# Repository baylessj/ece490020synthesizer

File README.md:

# ece490020synthesizer
PCB Layout and Schematics for an Analog Synthesizer for ECE Senior Design

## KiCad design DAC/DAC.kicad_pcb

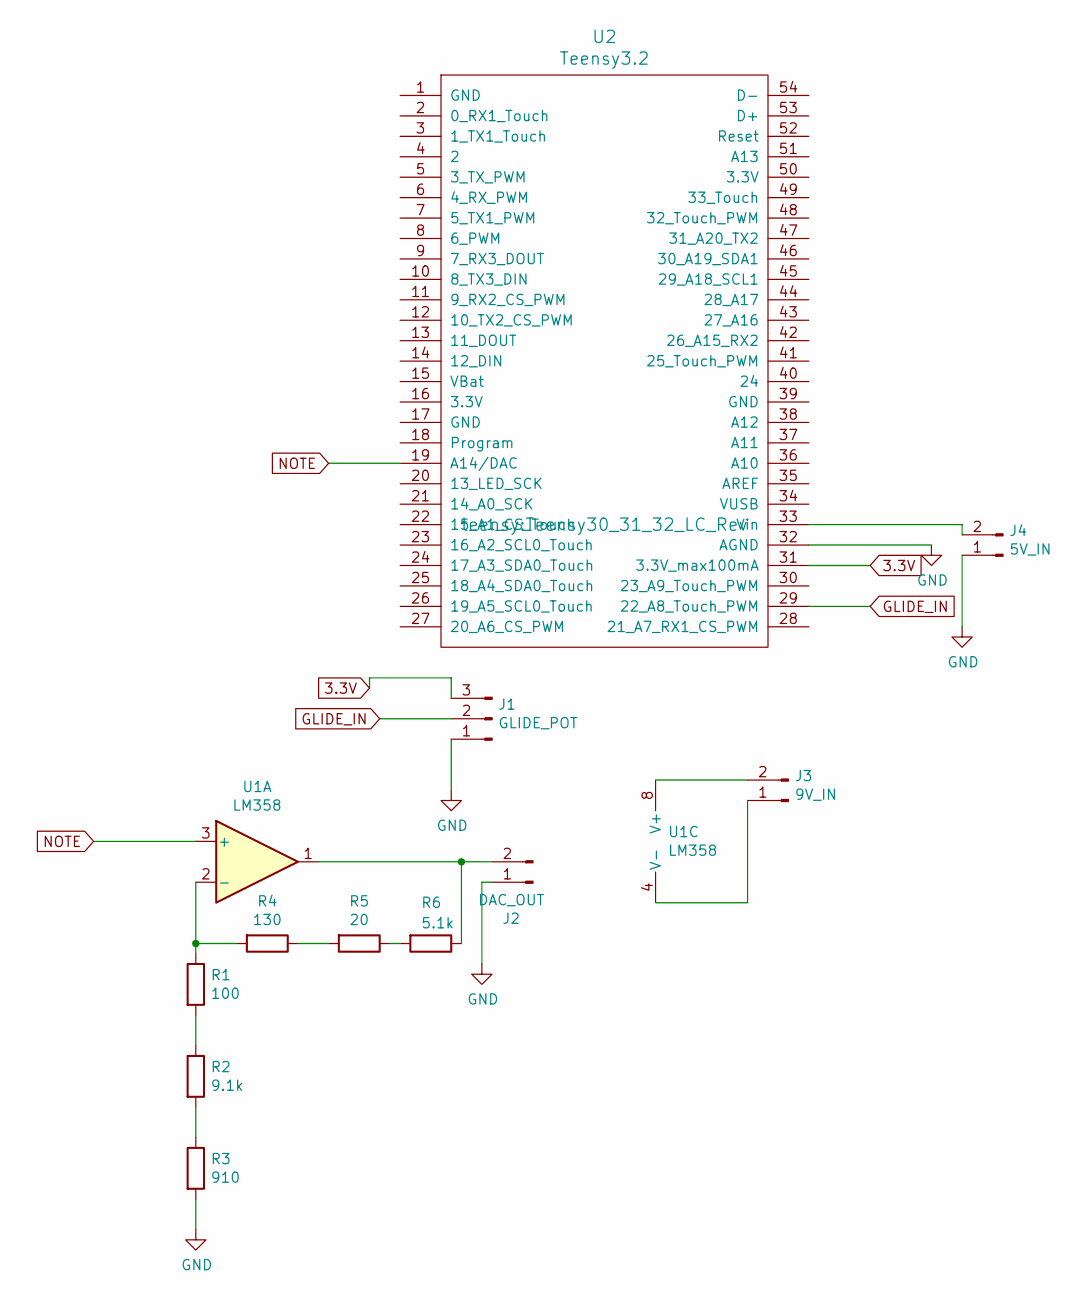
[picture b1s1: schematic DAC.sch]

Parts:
J1: GLIDE_POT; SolderWirePad_1x03_P3.175mm_Drill1mm
J2: DAC_OUT; SolderWirePad_1x02_P3.81mm_Drill1mm
J3: 9V_IN; SolderWirePad_1x02_P3.81mm_Drill1mm
J4: 5V_IN; SolderWirePad_1x02_P3.81mm_Drill1mm
R1: 100; R_Axial_DIN0207_L6.3mm_D2.5mm_P10.16mm_Horizontal
R2: 9.1k; R_Axial_DIN0207_L6.3mm_D2.5mm_P10.16mm_Horizontal
R3: 910; R_Axial_DIN0207_L6.3mm_D2.5mm_P10.16mm_Horizontal
R4: 130; R_Axial_DIN0207_L6.3mm_D2.5mm_P10.16mm_Horizontal
R5: 20; R_Axial_DIN0207_L6.3mm_D2.5mm_P10.16mm_Horizontal
R6: 5.1k; R_Axial_DIN0207_L6.3mm_D2.5mm_P10.16mm_Horizontal
U1: LM358; DIP-8_W7.62mm
U2: Teensy3.2; Teensy30_31_32_LC_Rev

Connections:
3.3V: J1.3, U2.31 (3.3V_max100mA)
GLIDE_IN: J1.2, U2.29 (22_A8_Touch_PWM)
GND: J1.1, J2.1, J4.1, R3.2, U2.32 (AGND)
NOTE: U1.3 (+), U2.19 (A14/DAC)
unnamed: J2.2, R6.1, U1.1
unnamed: J3.1, U1.4 (V-)
unnamed: J3.2, U1.8 (V+)
unnamed: J4.2, U2.33 (Vin)
unnamed: R1.1, R4.2, U1.2 (-)
unnamed: R1.2, R2.1
unnamed: R2.2, R3.1
unnamed: R4.1, R5.2
unnamed: R5.1, R6.2

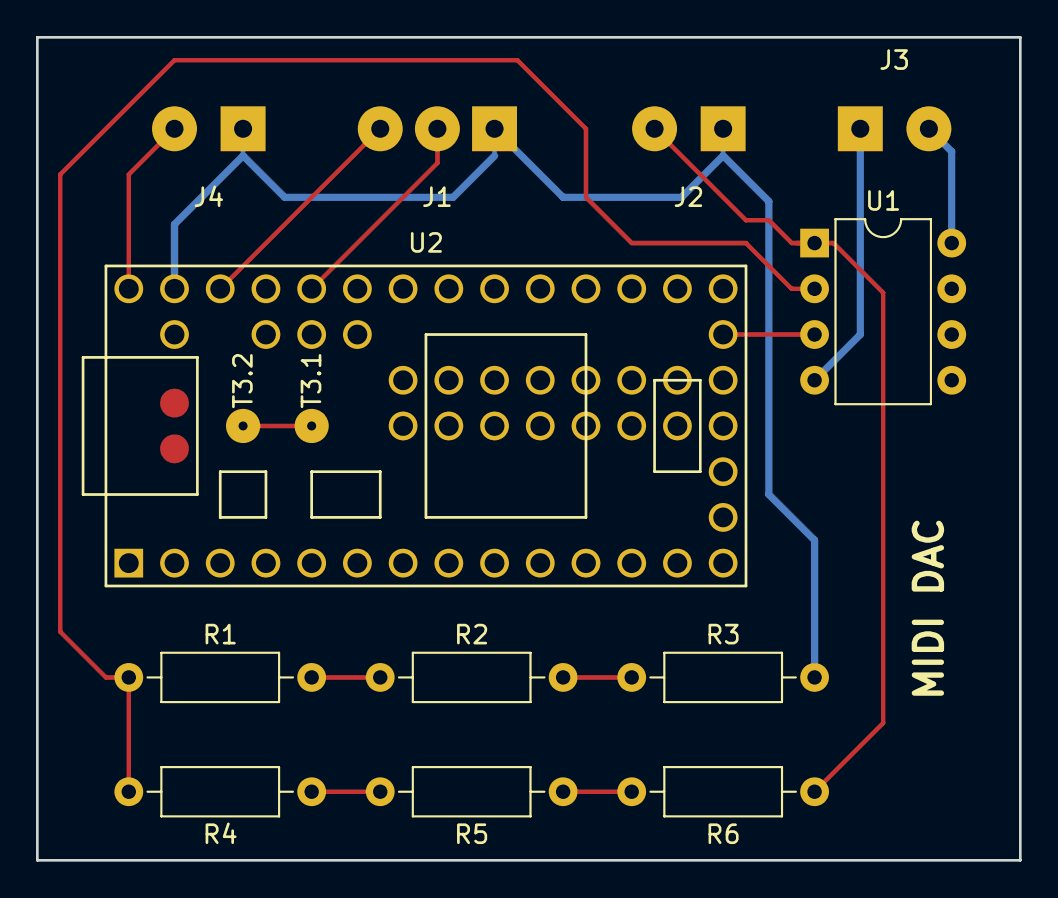
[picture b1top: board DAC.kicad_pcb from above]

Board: 2 copper layers, 54.6 x 45.7 mm, 12 parts (0 on the bottom side), 13 nets.

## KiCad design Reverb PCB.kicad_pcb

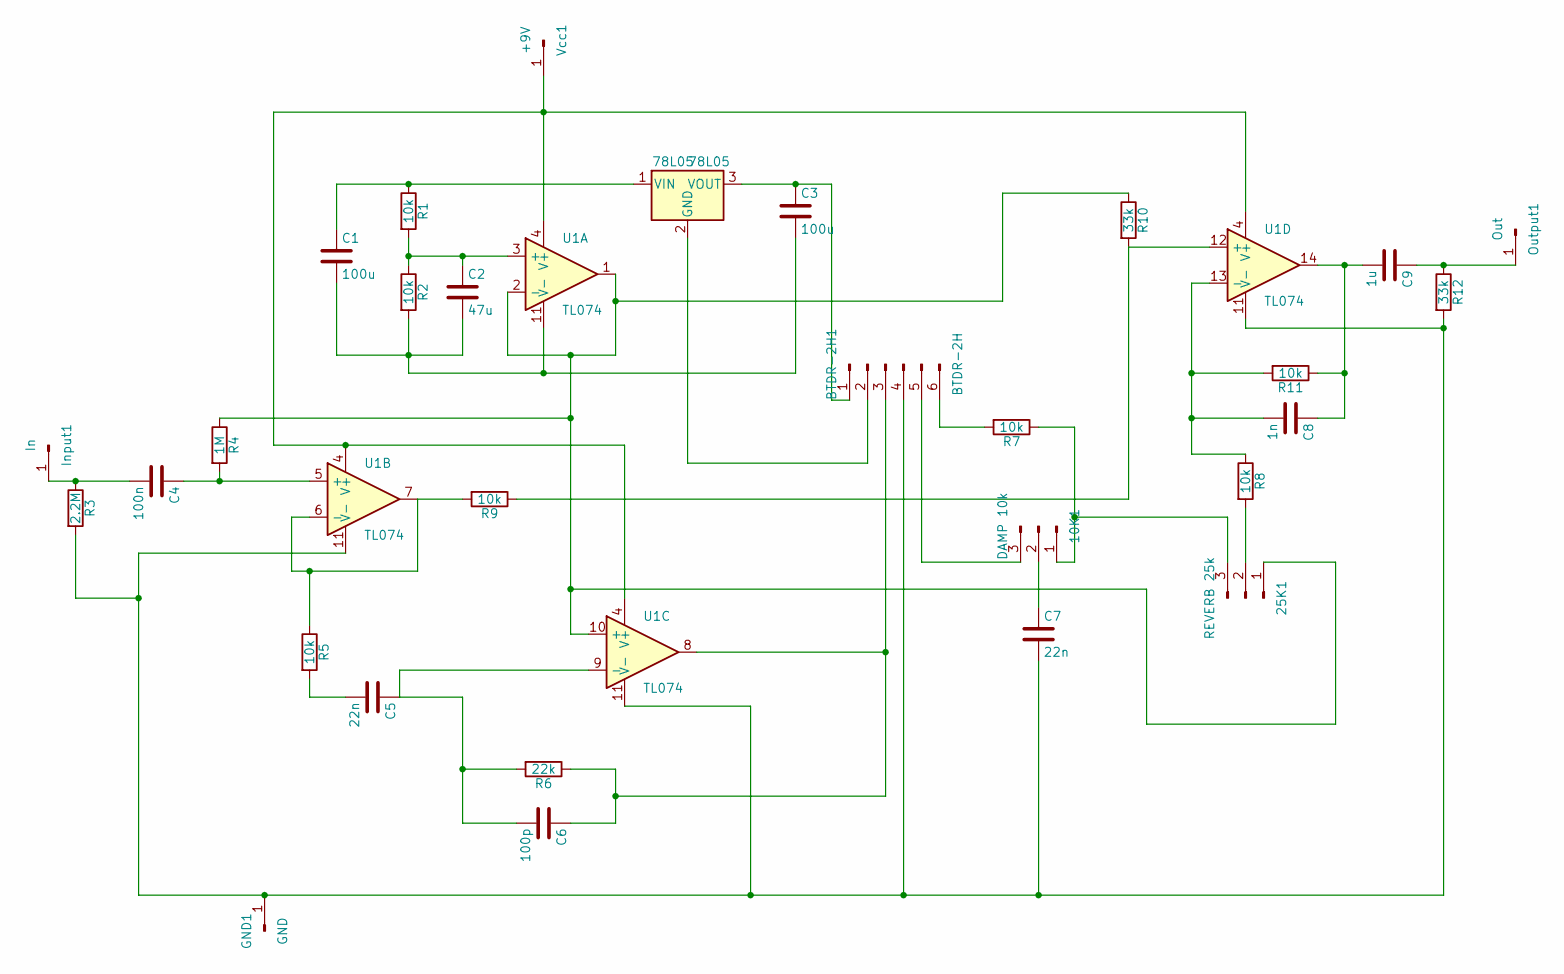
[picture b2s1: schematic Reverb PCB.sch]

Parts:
10K1: DAMP 10k; SolderWirePad_1x03_P3.175mm_Drill0.8mm
25K1: REVERB 25k; SolderWirePad_1x03_P3.175mm_Drill0.8mm
78L05: 78L05; TO-92_Inline_Narrow_Oval
BTDR-2H1: BTDR-2H; TerminalBlock_bornier-6_P5.08mm
C1, C3: 100u; CP_Radial_D10.0mm_P7.50mm
C2: 47u; CP_Radial_D8.0mm_P5.00mm
C4: 100n; C_Disc_D7.5mm_W5.0mm_P10.00mm
C5, C7: 22n; C_Disc_D7.5mm_W5.0mm_P10.00mm
C6: 100p; C_Disc_D7.5mm_W5.0mm_P10.00mm
C8: 1n; C_Disc_D7.5mm_W5.0mm_P10.00mm
C9: 1u; CP_Radial_D8.0mm_P5.00mm
GND1: GND; SolderWirePad_1x01_Drill0.8mm
Input1: In; SolderWirePad_1x01_Drill0.8mm
Output1: Out; SolderWirePad_1x01_Drill0.8mm
R1, R2, R5, R7, R8, R9, R11: 10k; R_Axial_DIN0207_L6.3mm_D2.5mm_P10.16mm_Horizontal
R3: 2.2M; R_Axial_DIN0207_L6.3mm_D2.5mm_P10.16mm_Horizontal
R4: 1M; R_Axial_DIN0207_L6.3mm_D2.5mm_P10.16mm_Horizontal
R6: 22k; R_Axial_DIN0207_L6.3mm_D2.5mm_P10.16mm_Horizontal
R10, R12: 33k; R_Axial_DIN0207_L6.3mm_D2.5mm_P10.16mm_Horizontal
U1: TL074; SW_DIP_x7_W7.62mm_Slide
Vcc1: +9V; SolderWirePad_1x01_Drill0.8mm

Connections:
unnamed: 10K1.1, 25K1.3, R7.1
unnamed: 10K1.2, C7.1
unnamed: 10K1.3, BTDR-2H1.5
unnamed: 25K1.1, R4.1, R10.1, U1.1, U1.2 (-), U1.10 (+)
unnamed: 25K1.2, R8.2
unnamed: 78L05.1 (VIN), C1.1, R1.1
unnamed: 78L05.2 (GND), BTDR-2H1.2
unnamed: 78L05.3 (VOUT), BTDR-2H1.1, C3.1
unnamed: BTDR-2H1.3, C6.1, R6.1, U1.8
unnamed: BTDR-2H1.6, R7.2
unnamed: C2.1, R1.2, R2.1, U1.3 (+)
unnamed: C4.1, R4.2, U1.5 (+)
unnamed: C4.2, Input1.1, R3.1
unnamed: C5.1, C6.2, R6.2, U1.9 (-)
unnamed: C5.2, R5.2
unnamed: C8.1, C9.2, R11.1, U1.14
unnamed: C8.2, R8.1, R11.2, U1.13 (-)
unnamed: C9.1, Output1.1, R12.1
unnamed: R5.1, R9.2, U1.6 (-), U1.7
unnamed: R9.1, R10.2, U1.12 (+)
unnamed: U1.4 (V+), Vcc1.1

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
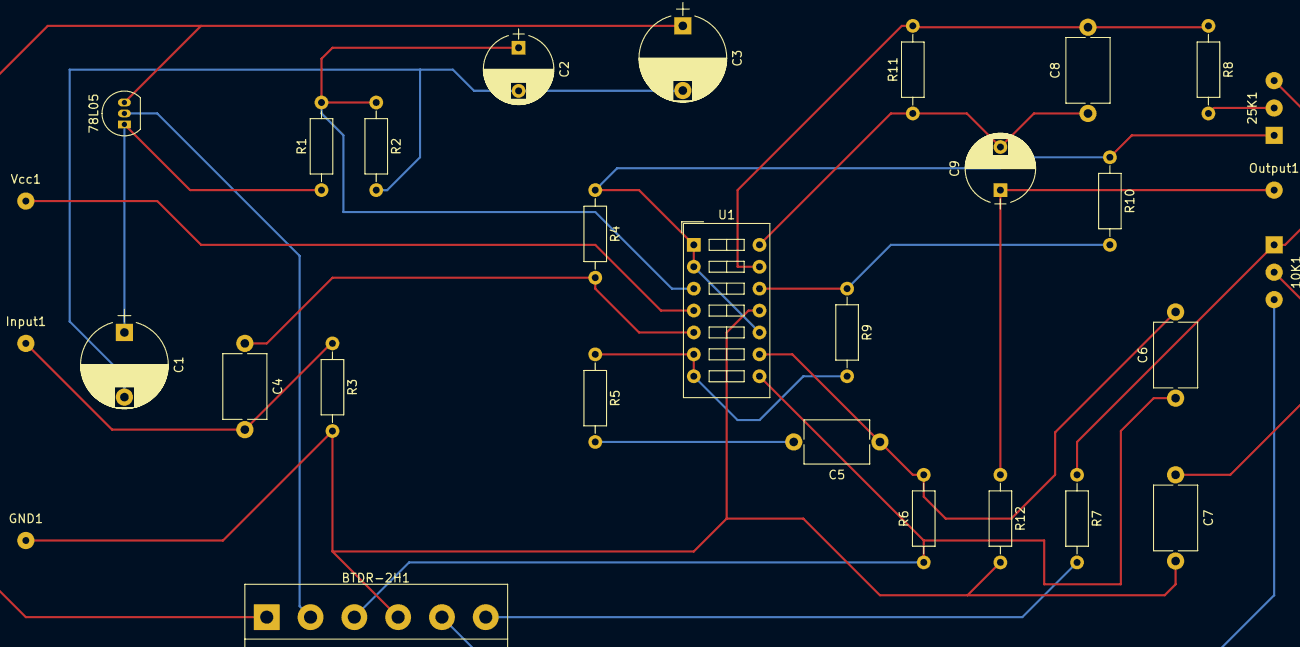
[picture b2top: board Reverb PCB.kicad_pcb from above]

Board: 2 copper layers, 30 parts (0 on the bottom side), 23 nets.

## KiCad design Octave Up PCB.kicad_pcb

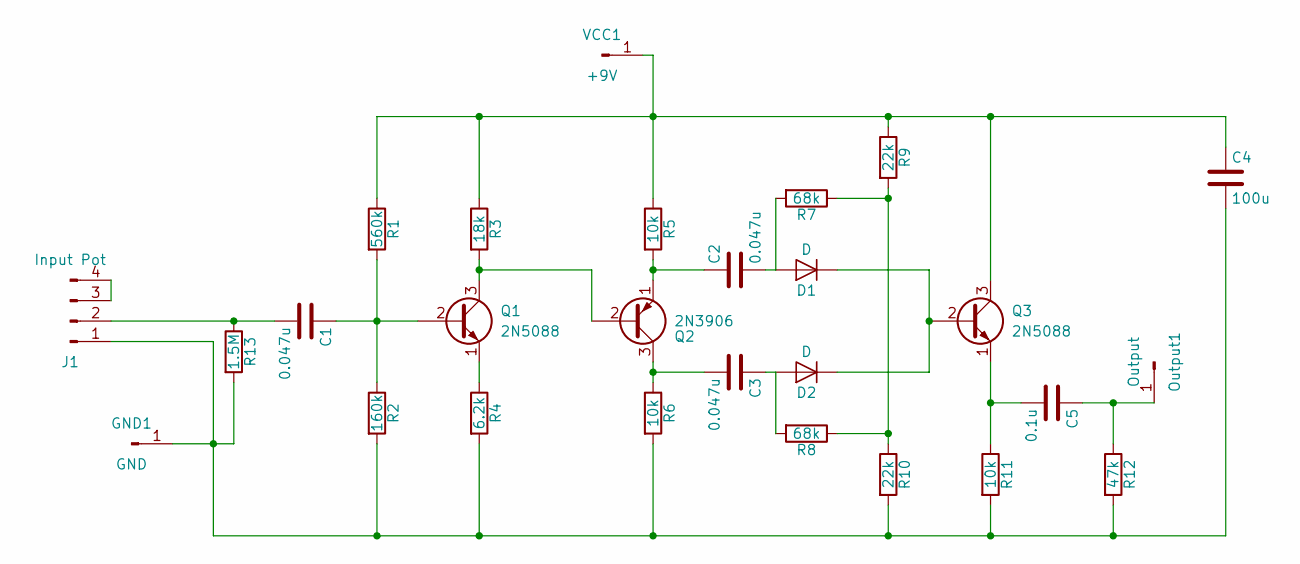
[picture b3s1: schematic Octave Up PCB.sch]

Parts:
C1, C2, C3: 0.047u; C_Axial_L3.8mm_D2.6mm_P10.00mm_Horizontal
C4: 100u; CP_Radial_D7.5mm_P2.50mm
C5: 0.1u; C_Rect_L7.5mm_W6.5mm_P5.00mm
D1, D2: D; D_A-405_P10.16mm_Horizontal
GND1: GND; SolderWirePad_1x01_Drill0.8mm
J1: Input Pot; SolderWirePad_1x04_P3.175mm_Drill0.8mm
Output1: Output; SolderWirePad_1x01_Drill0.8mm
Q1, Q3: 2N5088; TO-92_Inline_Narrow_Oval
Q2: 2N3906; TO-92_Inline_Narrow_Oval
R1: 560k; R_Axial_DIN0207_L6.3mm_D2.5mm_P10.16mm_Horizontal
R2: 160k; R_Axial_DIN0207_L6.3mm_D2.5mm_P10.16mm_Horizontal
R3: 18k; R_Axial_DIN0207_L6.3mm_D2.5mm_P10.16mm_Horizontal
R4: 6.2k; R_Axial_DIN0207_L6.3mm_D2.5mm_P10.16mm_Horizontal
R5, R6, R11: 10k; R_Axial_DIN0207_L6.3mm_D2.5mm_P10.16mm_Horizontal
R7, R8: 68k; R_Axial_DIN0207_L6.3mm_D2.5mm_P10.16mm_Horizontal
R9, R10: 22k; R_Axial_DIN0207_L6.3mm_D2.5mm_P10.16mm_Horizontal
R12: 47k; R_Axial_DIN0207_L6.3mm_D2.5mm_P10.16mm_Horizontal
R13: 1.5M; R_Axial_DIN0207_L6.3mm_D2.5mm_P10.16mm_Horizontal
VCC1: +9V; SolderWirePad_1x01_Drill0.8mm

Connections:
unnamed: C1.1, Q1.2 (B), R1.2, R2.1
unnamed: C1.2, J1.2, R13.1
unnamed: C2.1, Q2.1 (E), R5.2
unnamed: C2.2, D1.2 (A), R7.2
unnamed: C3.1, D2.2 (A), R8.2
unnamed: C3.2, Q2.3 (C), R6.1
unnamed: C4.1, Q3.3 (C), R1.1, R3.1, R5.1, R9.1, VCC1.1
unnamed: C4.2, GND1.1, J1.1, R2.2, R4.2, R6.2, R10.2, R11.2, R12.2, R13.2
unnamed: C5.1, Output1.1, R12.1
unnamed: C5.2, Q3.1 (E), R11.1
unnamed: D1.1 (K), D2.1 (K), Q3.2 (B)
unnamed: J1.3, J1.4
unnamed: Q1.1 (E), R4.1
unnamed: Q1.3 (C), Q2.2 (B), R3.2
unnamed: R7.1, R8.1, R9.2, R10.1

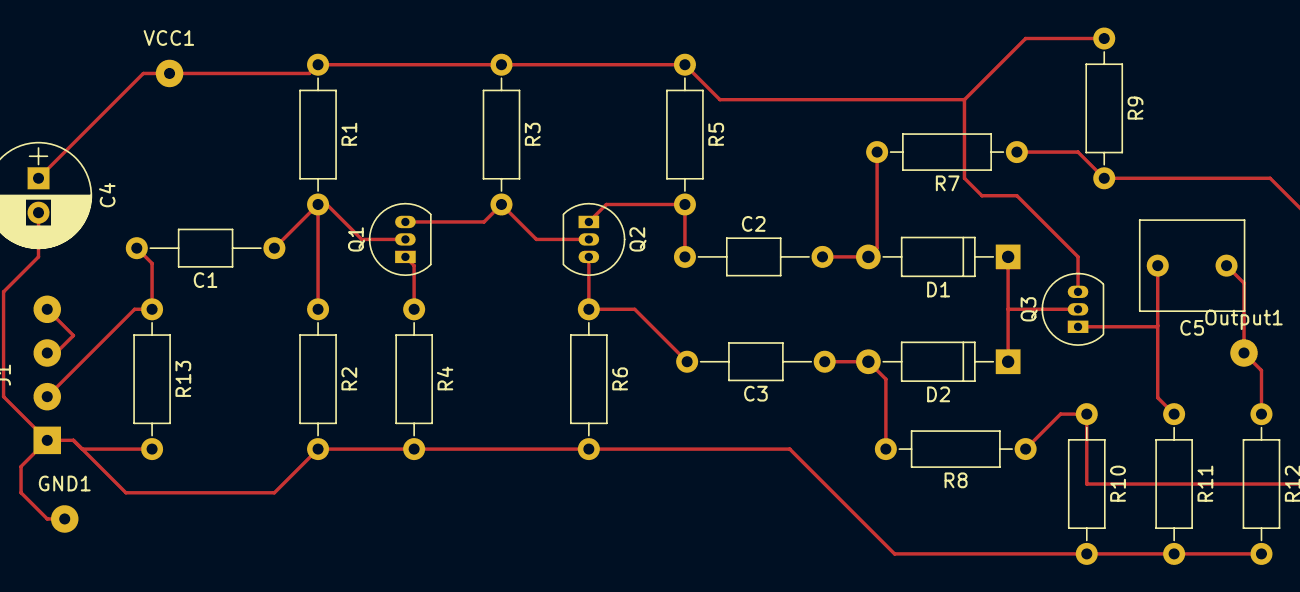
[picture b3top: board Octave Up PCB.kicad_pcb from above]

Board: 2 copper layers, 27 parts (0 on the bottom side), 15 nets.

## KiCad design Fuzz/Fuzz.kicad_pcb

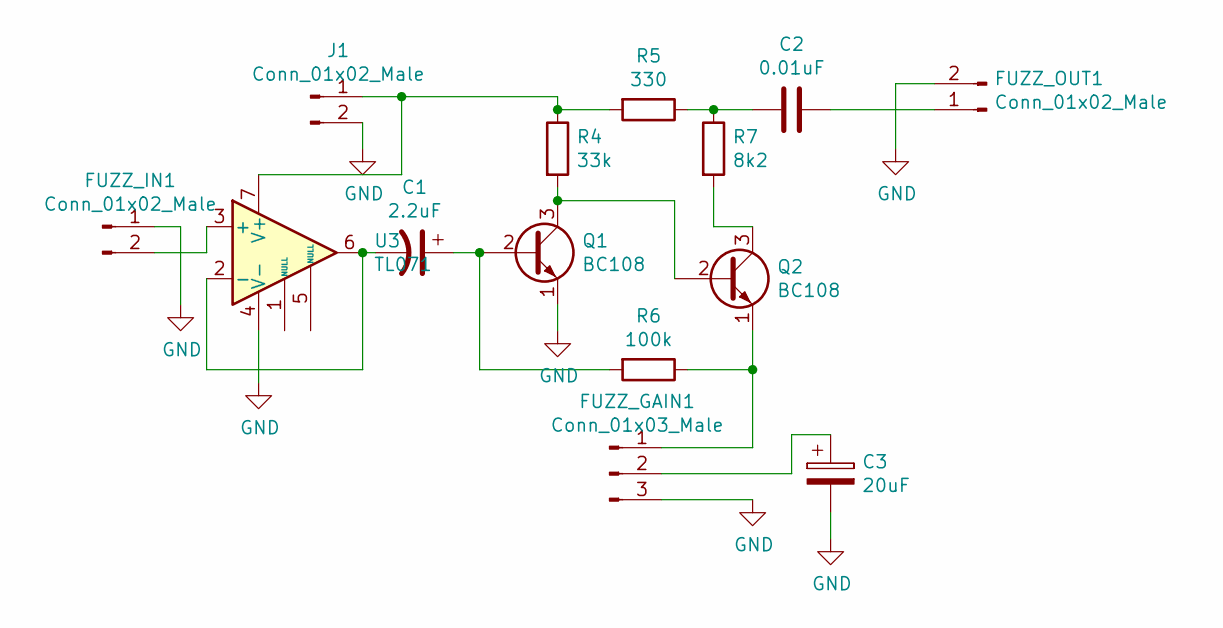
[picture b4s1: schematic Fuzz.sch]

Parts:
C1: 2.2uF; CP_Radial_D10.0mm_P5.00mm
C2: 0.01uF; C_Disc_D6.0mm_W2.5mm_P5.00mm
C3: 20uF; CP_Radial_D10.0mm_P5.00mm
FUZZ_GAIN1: Conn_01x03_Male; SolderWirePad_1x03_P4.445mm_Drill1.5mm
FUZZ_IN1: Conn_01x02_Male; SolderWirePad_1x02_P5.08mm_Drill1.5mm
FUZZ_OUT1: Conn_01x02_Male; SolderWirePad_1x02_P5.08mm_Drill1.5mm
J1: Conn_01x02_Male; SolderWirePad_1x02_P3.81mm_Drill1mm
Q1, Q2: BC108; TO-18-3
R4: 33k; R_Axial_DIN0207_L6.3mm_D2.5mm_P10.16mm_Horizontal
R5: 330; R_Axial_DIN0207_L6.3mm_D2.5mm_P10.16mm_Horizontal
R6: 100k; R_Axial_DIN0207_L6.3mm_D2.5mm_P10.16mm_Horizontal
R7: 8k2; R_Axial_DIN0207_L6.3mm_D2.5mm_P10.16mm_Horizontal
U3: TL071; DIP-8_W7.62mm_Socket

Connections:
GND: C3.2, FUZZ_GAIN1.3, FUZZ_IN1.1, FUZZ_OUT1.2, J1.2, Q1.1 (E), U3.4 (V-)
unnamed: C1.1, Q1.2 (B), R6.2
unnamed: C1.2, U3.2 (-), U3.6
unnamed: C2.1, FUZZ_OUT1.1
unnamed: C2.2, R5.1, R7.1
unnamed: C3.1, FUZZ_GAIN1.2
unnamed: FUZZ_GAIN1.1, Q2.1 (E), R6.1
unnamed: FUZZ_IN1.2, U3.3 (+)
unnamed: J1.1, R4.1, R5.2, U3.7 (V+)
unnamed: Q1.3 (C), Q2.2 (B), R4.2
unnamed: Q2.3 (C), R7.2

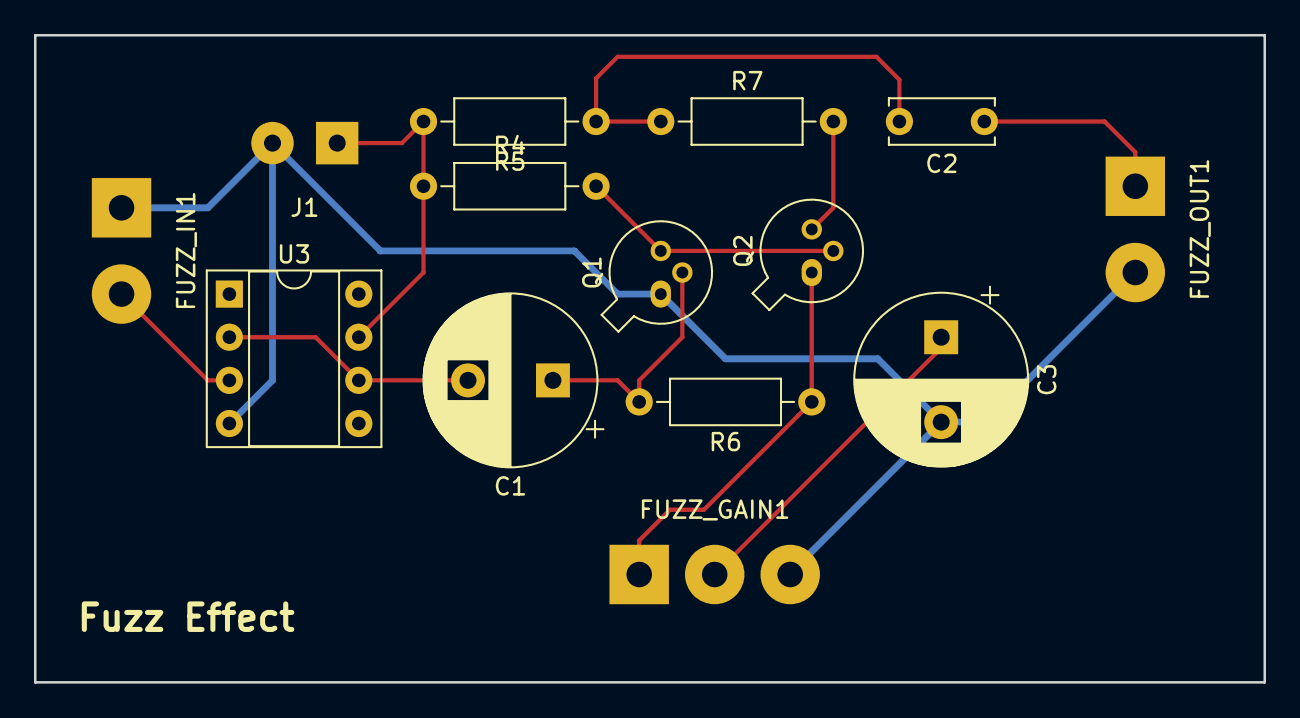
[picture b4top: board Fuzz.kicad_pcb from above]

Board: 2 copper layers, 72.4 x 38.1 mm, 14 parts (0 on the bottom side), 11 nets.

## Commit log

2019-02-01 Add blank KiCad project
2019-02-01 Add Teensy Library and Teensy3.6 to sch
2019-02-01 Poorly laid out MIDI DAC subsystem
2019-02-01 Fuzz Face schematic added
2019-02-06 Clean up DAC schematic
2019-02-06 Add fuzz volume trim pot
2019-02-08 made some progress on testing, still an odd waveform though
2019-02-13 Getting a decent square wave now
2019-02-20 Create rats nest for pcb layout
2019-03-08 Add buffer for fuzz
2019-03-08 Remove DAC circuit
2019-03-08 Remove Synthesizer project
2019-03-08 Arrange pcb components
2019-03-20 PCB tracks set
2019-03-20 Board is laid out
2019-03-20 Various files for PCB review
2019-03-20 Add PCB review components
2019-04-23 not sure what this is tbh
